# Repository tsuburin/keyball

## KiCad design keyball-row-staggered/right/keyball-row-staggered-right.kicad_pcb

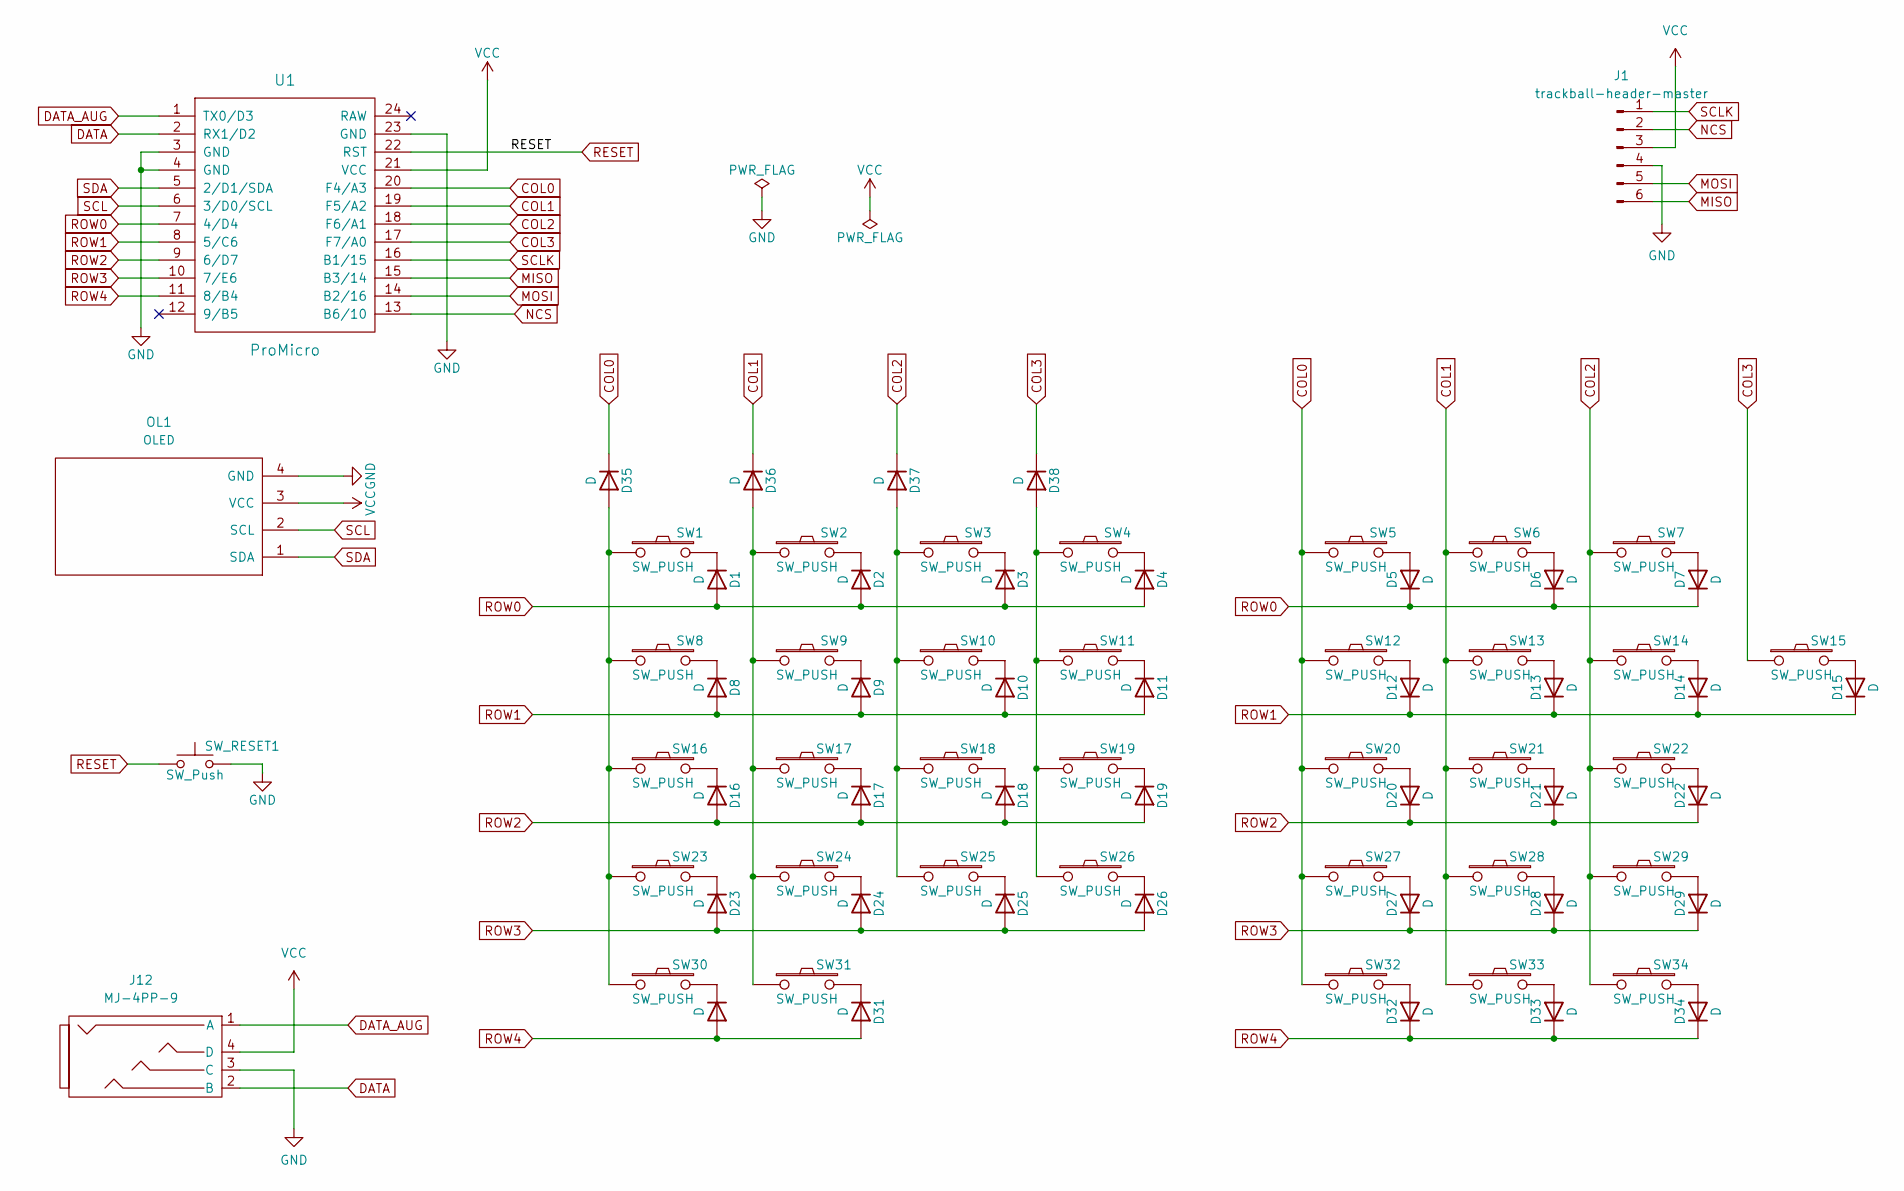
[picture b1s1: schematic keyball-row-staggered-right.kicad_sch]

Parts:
D1, D2, D3, D4, D5, D6, D7, D8, D9, D10, D11, D12, D13, D14, D15, D16, D17, D18, D19, D20, D21, D22, D23, D24, D25, D26, D27, D28, D29, D30, D31, D32, D33, D34, D35, D36, D37, D38: D; D3_SMD_v2
J1: trackball-header-master; keyball_trackball_header_master
J12: MJ-4PP-9
OL1: OLED; OLED_v2
SW1, SW2, SW3, SW4, SW5, SW6, SW7, SW8, SW9, SW10, SW11, SW12, SW13, SW14, SW15, SW16, SW17, SW18, SW19, SW20, SW21, SW22, SW23, SW24, SW25, SW26, SW27, SW28, SW29, SW32, SW33, SW34: SW_PUSH; Kailh_socket_MX
SW30, SW31: SW_PUSH; CherryMX_Choc_Hotswap
SW_RESET1: SW_Push; ResetSW_1side
U1: ProMicro; ProMicro_v3

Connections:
COL0: D35.1 (K), SW5.1, SW12.1, SW20.1, SW27.1, SW32.1, U1.20 (F4/A3)
COL1: D36.1 (K), SW6.1, SW13.1, SW21.1, SW28.1, SW33.1, U1.19 (F5/A2)
COL2: D37.1 (K), SW7.1, SW14.1, SW22.1, SW29.1, SW34.1, U1.18 (F6/A1)
COL3: D38.1 (K), SW15.1, U1.17 (F7/A0)
DATA: J12.2 (B), U1.2 (RX1/D2)
DATA_AUG: J12.1 (A), U1.1 (TX0/D3)
GND: J1.4 (GND), J12.3 (C), OL1.4 (GND), SW_RESET1.2, U1.3 (GND), U1.4 (GND), U1.23 (GND)
MISO: J1.6 (MISO), U1.15 (B3/14)
MOSI: J1.5 (MOSI), U1.14 (B2/16)
NCS: J1.2 (NCS), U1.13 (B6/10)
unnamed: D1.1 (K), SW1.2
unnamed: D2.1 (K), SW2.2
unnamed: D3.1 (K), SW3.2
unnamed: D4.1 (K), SW4.2
unnamed: D5.2 (A), SW5.2
unnamed: D6.2 (A), SW6.2
unnamed: D7.2 (A), SW7.2
unnamed: D8.1 (K), SW8.2
unnamed: D9.1 (K), SW9.2
unnamed: D10.1 (K), SW10.2
unnamed: D11.1 (K), SW11.2
unnamed: D12.2 (A), SW12.2
unnamed: D13.2 (A), SW13.2
unnamed: D14.2 (A), SW14.2
unnamed: D15.2 (A), SW15.2
unnamed: D16.1 (K), SW16.2
unnamed: D17.1 (K), SW17.2
unnamed: D18.1 (K), SW18.2
unnamed: D19.1 (K), SW19.2
unnamed: D20.2 (A), SW20.2
unnamed: D21.2 (A), SW21.2
unnamed: D22.2 (A), SW22.2
unnamed: D23.1 (K), SW23.2
unnamed: D24.1 (K), SW24.2
unnamed: D25.1 (K), SW25.2
unnamed: D26.1 (K), SW26.2
unnamed: D27.2 (A), SW27.2
unnamed: D28.2 (A), SW28.2
unnamed: D29.2 (A), SW29.2
unnamed: D30.1 (K), SW30.2
unnamed: D31.1 (K), SW31.2
unnamed: D32.2 (A), SW32.2
unnamed: D33.2 (A), SW33.2
unnamed: D34.2 (A), SW34.2
unnamed: D35.2 (A), SW1.1, SW8.1, SW16.1, SW23.1, SW30.1
unnamed: D36.2 (A), SW2.1, SW9.1, SW17.1, SW24.1, SW31.1
unnamed: D37.2 (A), SW3.1, SW10.1, SW18.1, SW25.1
unnamed: D38.2 (A), SW4.1, SW11.1, SW19.1, SW26.1
RESET: SW_RESET1.1, U1.22 (RST)
ROW0: D1.2 (A), D2.2 (A), D3.2 (A), D4.2 (A), D5.1 (K), D6.1 (K), D7.1 (K), U1.7 (4/D4)
ROW1: D8.2 (A), D9.2 (A), D10.2 (A), D11.2 (A), D12.1 (K), D13.1 (K), D14.1 (K), D15.1 (K), U1.8 (5/C6)
ROW2: D16.2 (A), D17.2 (A), D18.2 (A), D19.2 (A), D20.1 (K), D21.1 (K), D22.1 (K), U1.9 (6/D7)
ROW3: D23.2 (A), D24.2 (A), D25.2 (A), D26.2 (A), D27.1 (K), D28.1 (K), D29.1 (K), U1.10 (7/E6)
ROW4: D30.2 (A), D31.2 (A), D32.1 (K), D33.1 (K), D34.1 (K), U1.11 (8/B4)
SCL: OL1.2 (SCL), U1.6 (3/D0/SCL)
SCLK: J1.1 (SCLK), U1.16 (B1/15)
SDA: OL1.1 (SDA), U1.5 (2/D1/SDA)
VCC: J1.3 (VCC), J12.4 (D), OL1.3 (VCC), U1.21 (VCC)

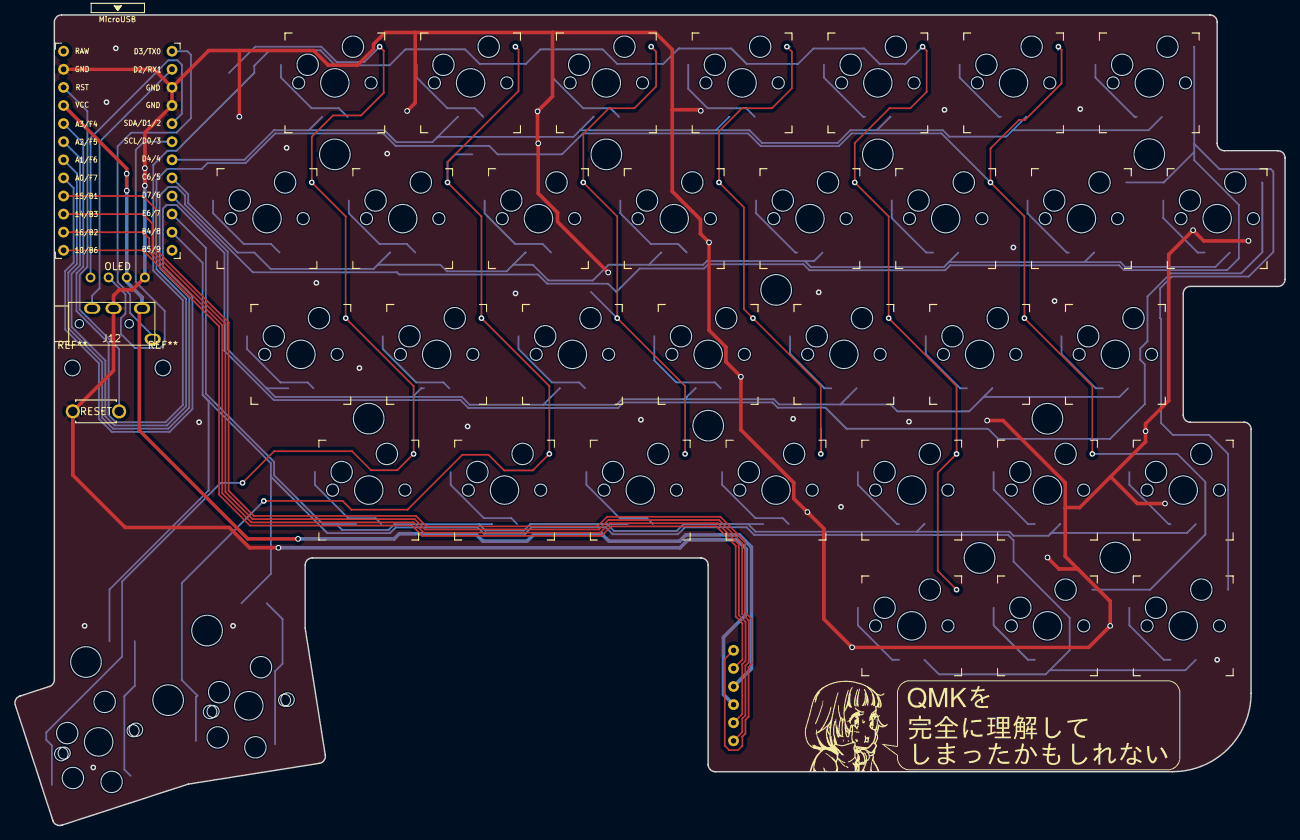
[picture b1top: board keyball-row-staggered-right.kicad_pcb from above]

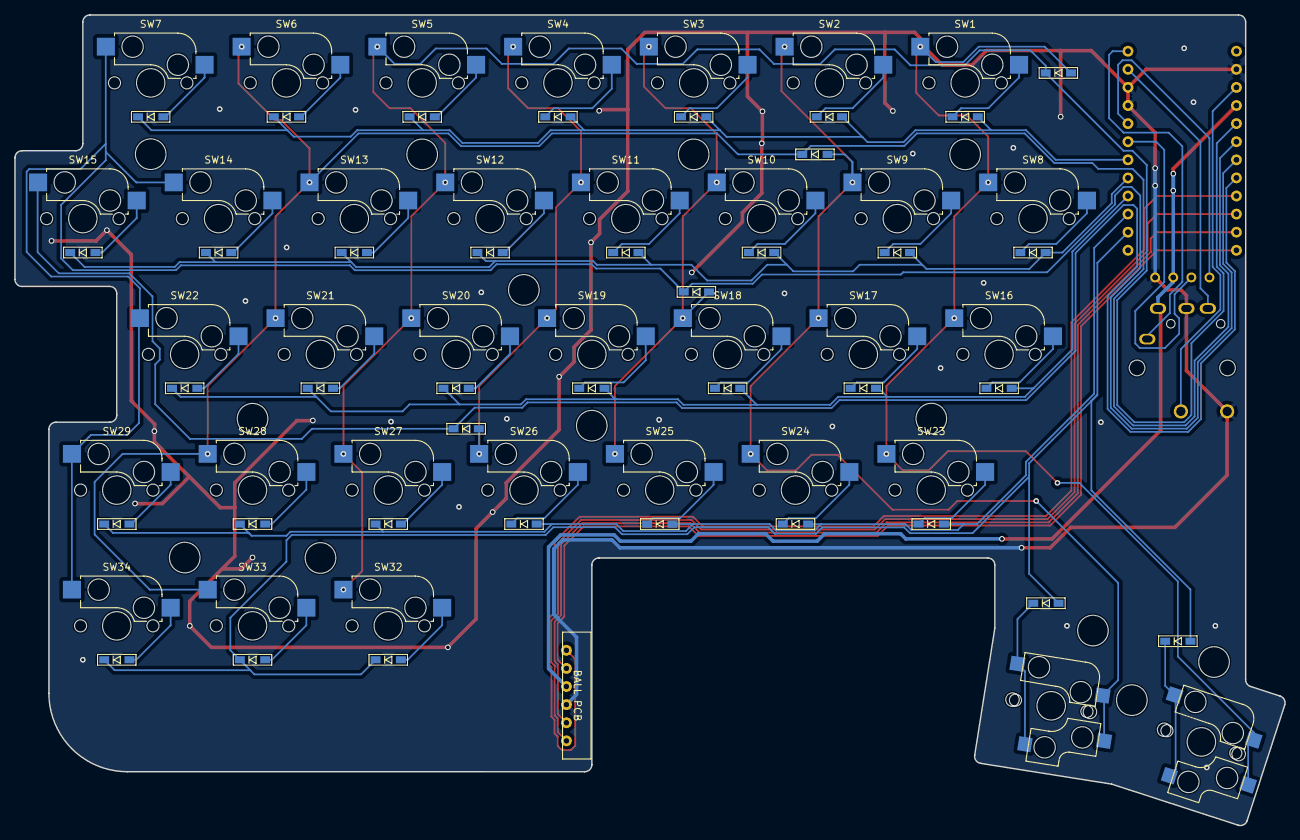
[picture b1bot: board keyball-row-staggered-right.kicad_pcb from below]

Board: 2 copper layers, 178.2 x 113.8 mm, 90 parts (38 on the bottom side), 58 nets.

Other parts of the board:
Ref**: Val**; spacer_m2
Ref**#2, Ref**#3, Ref**#4, Ref**#5, Ref**#6, Ref**#7, Ref**#8, Ref**#9, Ref**#10, Ref**#11, Ref**#12, Ref**#13: Val**; spacer_m2
